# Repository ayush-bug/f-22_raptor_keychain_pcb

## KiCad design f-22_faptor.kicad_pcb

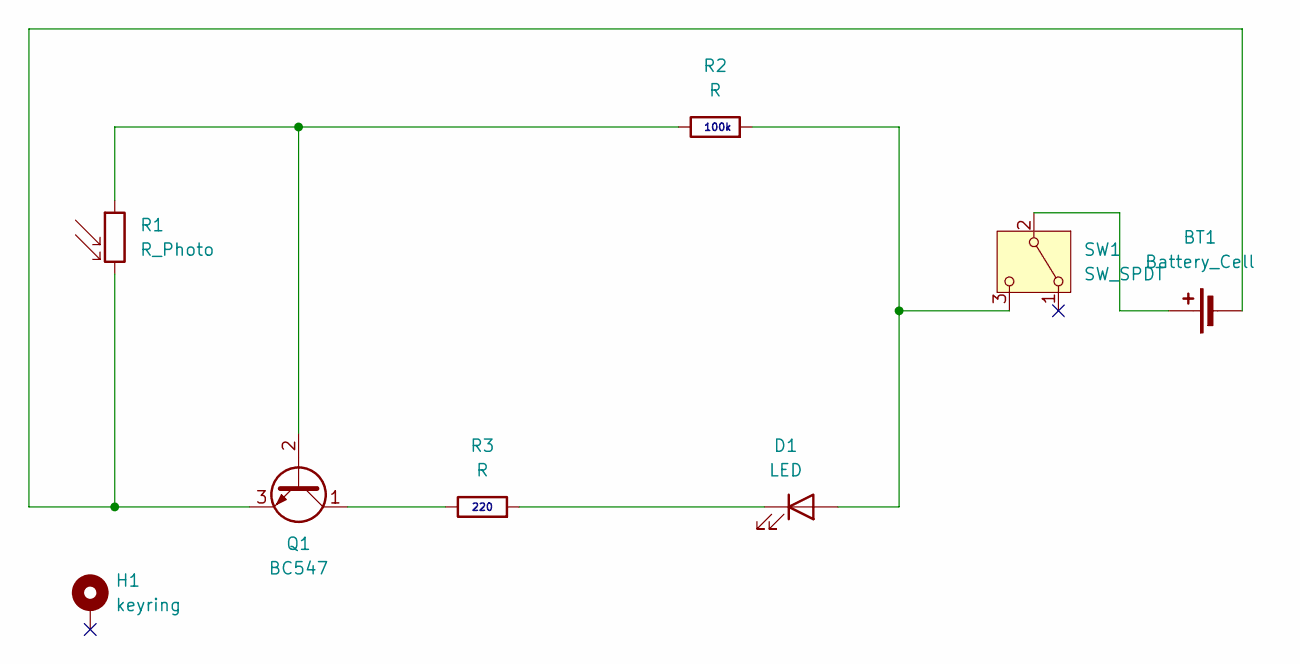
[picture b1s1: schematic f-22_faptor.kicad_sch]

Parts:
BT1: Battery_Cell; BatteryHolder_Keystone_3002_1x2032
D1: LED; LED_D3.0mm
H1: keyring; MountingHole_2.2mm_M2_Pad_Via
Q1: BC547; TO-92L_Inline_Wide
R1: R_Photo; R_LDR_10x8.5mm_P7.6mm_Vertical
R2, R3: R; R_Axial_DIN0207_L6.3mm_D2.5mm_P7.62mm_Horizontal
SW1: SW_SPDT; SW_Slide-03_Wuerth-WS-SLTV_10x2.5x6.4_P2.54mm

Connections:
unnamed: BT1.1 (+), SW1.2 (B)
unnamed: BT1.2 (-), Q1.3 (E), R1.2
unnamed: D1.2 (A), R2.2, SW1.3 (C)
unnamed: D1.1 (K), R3.2
unnamed: Q1.2 (B), R1.1, R2.1
unnamed: Q1.1 (C), R3.1

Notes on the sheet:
100k
220

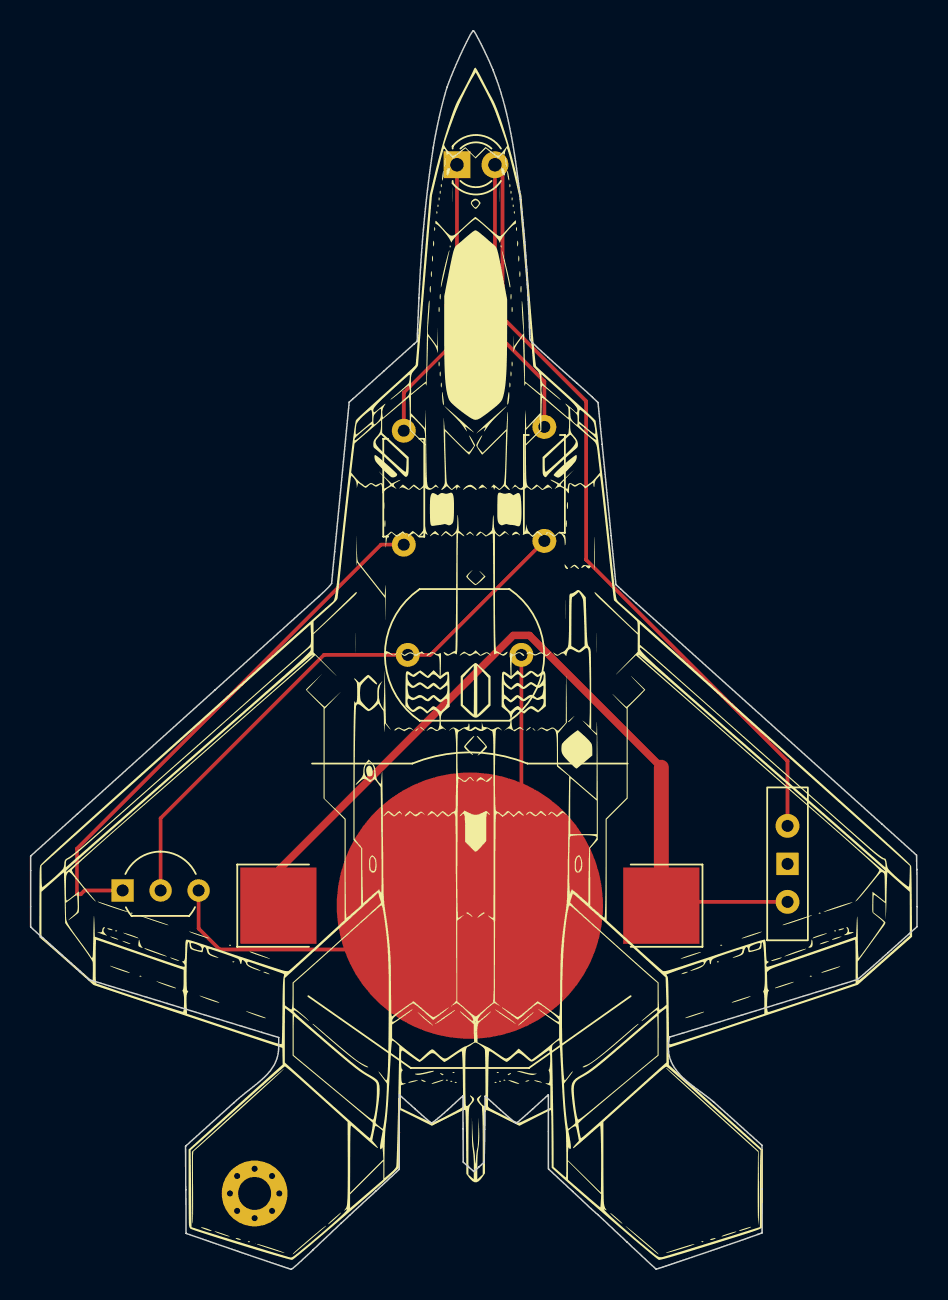
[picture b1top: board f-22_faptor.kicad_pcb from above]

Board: 2 copper layers, 59.3 x 82.8 mm, 8 parts (0 on the bottom side), 6 nets.
